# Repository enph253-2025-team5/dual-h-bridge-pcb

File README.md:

# Dual H-Bridge PCB

Dual h-bridge design with a PWM signal and direction bit for controlling two motors.

Similar to Greg Reid's 2025 h-bridge design, without relying on tripping the overcurrent protection. Instead, this design duplicates the incoming PWM signal, sends one to each of the low side h-bridge MOSFETs, then pulls the gate with the enhanced high side MOSFET low (avoiding shoot-through). 

Based on many factors (motor inertia, gate driver response, optocoupler distortion) the PWM frequency should be limited on the order of 100 Hz.
Intended motor battery configuration of 4S.

**BOM, Schematic, and PCB drawings in the latest release.**

## Images

Designed by George Sleen.

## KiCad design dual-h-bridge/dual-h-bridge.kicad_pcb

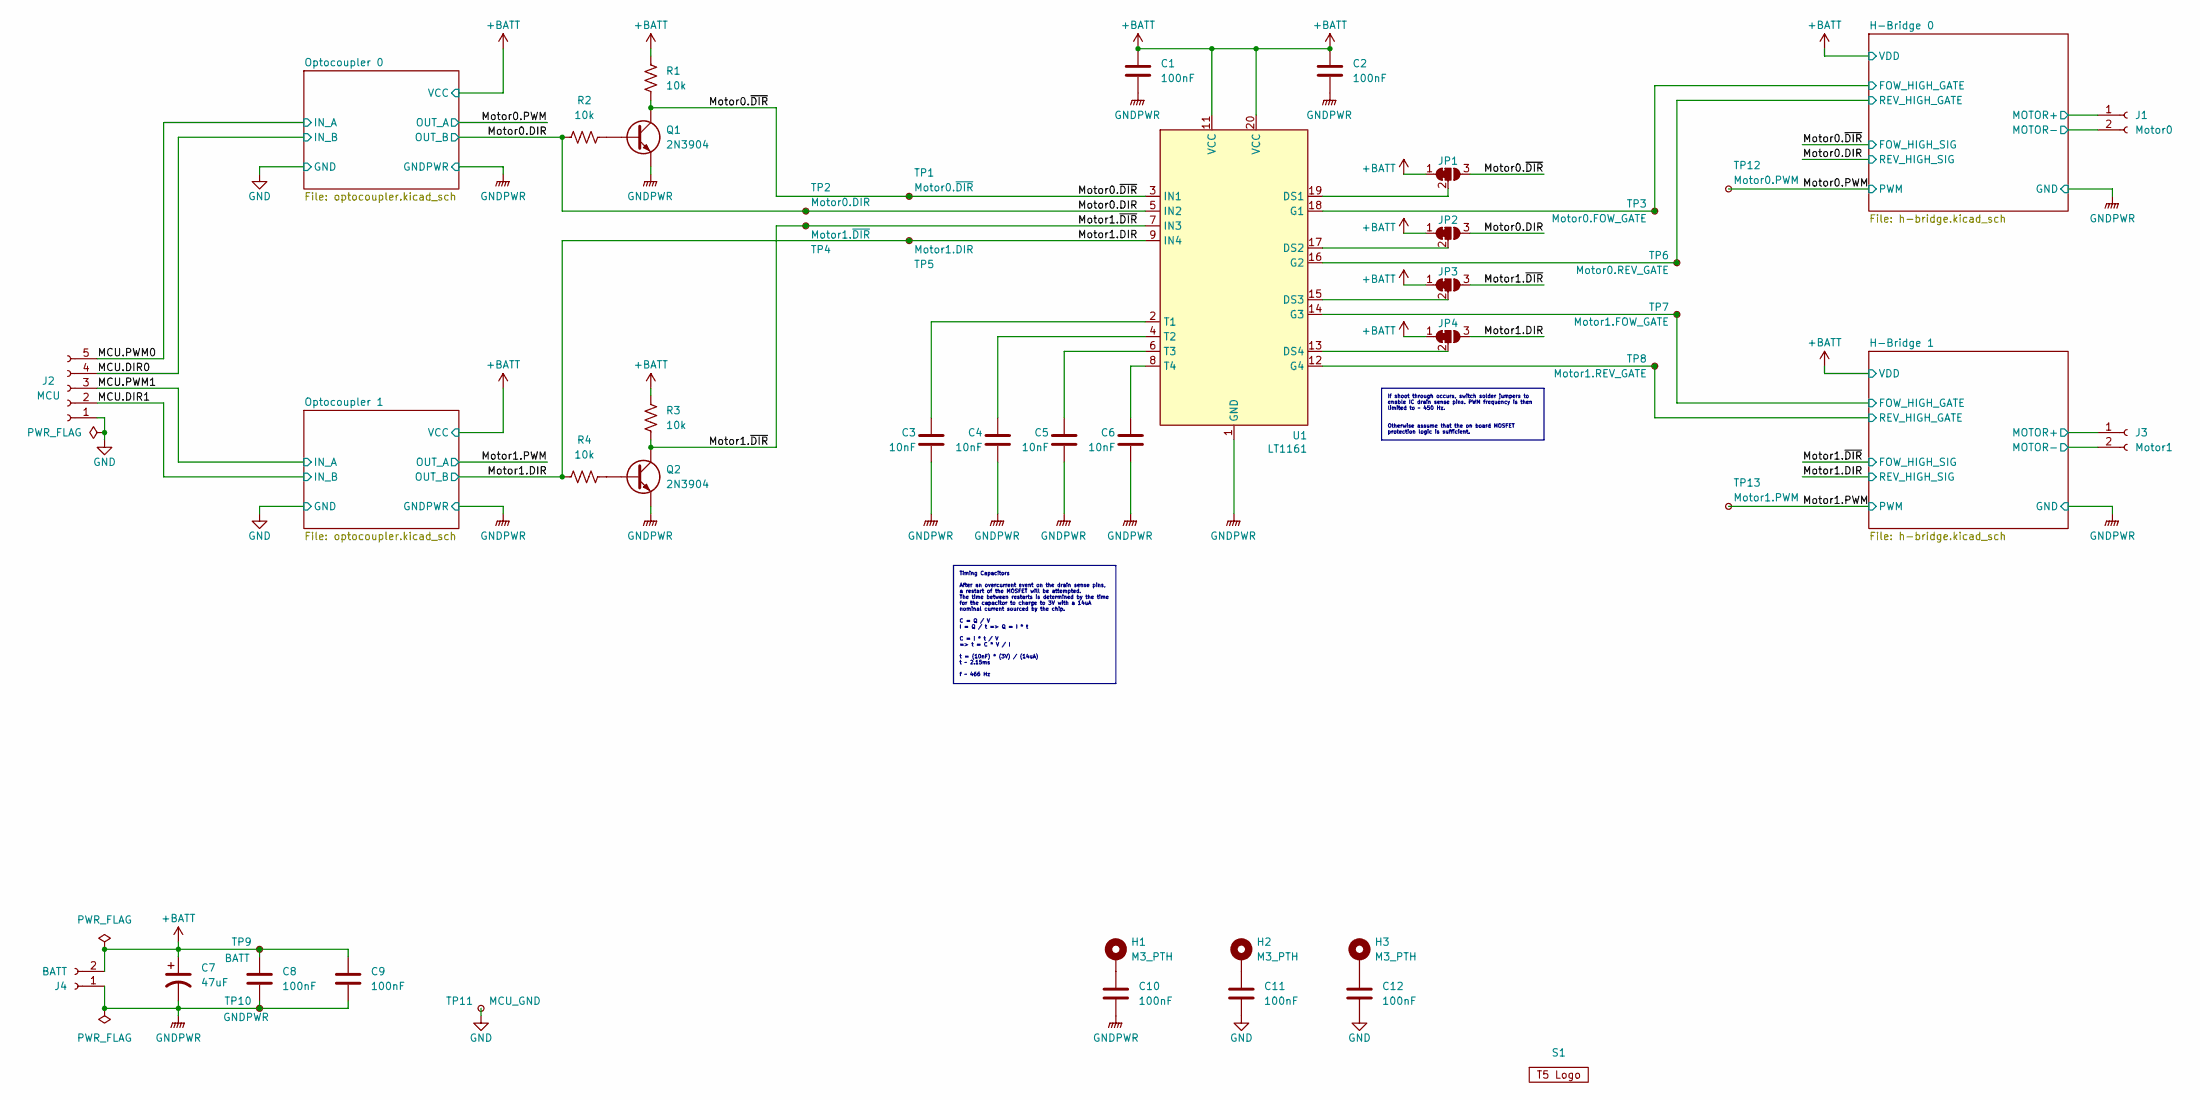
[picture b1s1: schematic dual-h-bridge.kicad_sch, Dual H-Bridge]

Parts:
C1, C2, C8, C9, C10, C11, C12: 100nF; C_Disc_D3.0mm_W2.0mm_P2.50mm
C3, C4, C5, C6: 10nF; C_Disc_D3.0mm_W2.0mm_P2.50mm
C7: 47uF; CP_Radial_D5.0mm_P2.00mm
H1, H2, H3: M3_PTH; MountingHole_3.2mm_M3_Pad
J1: Motor0; JST_XH_S2B-XH-A-1_1x02_P2.50mm_Horizontal
J2: MCU; JST_XH_B5B-XH-A_1x05_P2.50mm_Vertical
J3: Motor1; JST_XH_S2B-XH-A-1_1x02_P2.50mm_Horizontal
J4: BATT; JST_XH_B2B-XH-A_1x02_P2.50mm_Vertical
JP1: Motor0_FOW; SolderJumper-3_P1.3mm_Bridged12_RoundedPad1.0x1.5mm
JP2: MOTOR0_REV; SolderJumper-3_P1.3mm_Bridged12_RoundedPad1.0x1.5mm
JP3: MOTOR1_FOW; SolderJumper-3_P1.3mm_Bridged12_RoundedPad1.0x1.5mm
JP4: MOTOR1_REV; SolderJumper-3_P1.3mm_Bridged12_RoundedPad1.0x1.5mm
Q1, Q2: 2N3904; TO-92_Inline
R1, R2, R3, R4: 10k; R_Axial_DIN0309_L9.0mm_D3.2mm_P12.70mm_Horizontal
S1: Logo; ENPH253_Logo_Small
TP1: Motor0.~{DIR}; TestPoint_Pad_1.5x1.5mm
TP2: Motor0.DIR; TestPoint_Pad_1.5x1.5mm
TP3: Motor0.FOW_GATE; TestPoint_Pad_1.5x1.5mm
TP4: Motor1.~{DIR}; TestPoint_Pad_1.5x1.5mm
TP5: Motor1.DIR; TestPoint_Pad_1.5x1.5mm
TP6: Motor0.REV_GATE; TestPoint_Pad_1.5x1.5mm
TP7: Motor1.FOW_GATE; TestPoint_Pad_1.5x1.5mm
TP8: Motor1.REV_GATE; TestPoint_Pad_1.5x1.5mm
TP9: BATT; TestPoint_Pad_1.5x1.5mm
TP10: GNDPWR; TestPoint_Pad_1.5x1.5mm
TP11: MCU_GND; TestPoint_Pad_1.5x1.5mm
TP12: Motor0.PWM; TestPoint_Pad_1.5x1.5mm
TP13: Motor1.PWM; TestPoint_Pad_1.5x1.5mm
U1: LT1161; DIP-20_W7.62mm_LongPads

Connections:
+BATT: C1.1, C2.1, C7.1, C8.1, C9.1, J4.2, JP1.1 (A), JP2.1 (A), JP3.1 (A), JP4.1 (A), R1.1, R3.1, TP9.1, U1.11 (VCC), U1.20 (VCC); also elsewhere on the board
/H-Bridge 0/FOW_HIGH_GATE: TP3.1, U1.18 (G1); also elsewhere on the board
/H-Bridge 0/MOTOR+: J1.1; also elsewhere on the board
/H-Bridge 0/MOTOR-: J1.2; also elsewhere on the board
/H-Bridge 0/REV_HIGH_GATE: TP6.1, U1.16 (G2); also elsewhere on the board
/H-Bridge 1/FOW_HIGH_GATE: TP7.1, U1.14 (G3); also elsewhere on the board
/H-Bridge 1/MOTOR+: J3.1; also elsewhere on the board
/H-Bridge 1/MOTOR-: J3.2; also elsewhere on the board
/H-Bridge 1/REV_HIGH_GATE: TP8.1, U1.12 (G4); also elsewhere on the board
/MCU.DIR0: J2.4; also elsewhere on the board
/MCU.DIR1: J2.2; also elsewhere on the board
/MCU.PWM0: J2.5; also elsewhere on the board
/MCU.PWM1: J2.3; also elsewhere on the board
/Motor0.DIR: JP2.3 (B), R2.1, TP2.1, U1.5 (IN2); also elsewhere on the board
/Motor0.PWM: TP12.1; also elsewhere on the board
/Motor0.~DIR: JP1.3 (B), Q1.3 (C), R1.2, TP1.1, U1.3 (IN1); also elsewhere on the board
/Motor1.DIR: JP4.3 (B), R4.1, TP5.1, U1.9 (IN4); also elsewhere on the board
/Motor1.PWM: TP13.1; also elsewhere on the board
/Motor1.~DIR: JP3.3 (B), Q2.3 (C), R3.2, TP4.1, U1.7 (IN3); also elsewhere on the board
GND: C11.2, C12.2, J2.1, TP11.1; also elsewhere on the board
GNDPWR: C1.2, C2.2, C3.2, C4.2, C5.2, C6.2, C7.2, C8.2, C9.2, C10.2, J4.1, Q1.1 (E), Q2.1 (E), TP10.1, U1.1 (GND), U1.10 (GND); also elsewhere on the board
unnamed: C10.1, H1.1
unnamed: C11.1, H2.1
unnamed: C12.1, H3.1
unnamed: JP1.2 (C), U1.19 (DS1)
unnamed: JP2.2 (C), U1.17 (DS2)
unnamed: JP3.2 (C), U1.15 (DS3)
unnamed: JP4.2 (C), U1.13 (DS4)
unnamed: Q1.2 (B), R2.2
unnamed: Q2.2 (B), R4.2
unnamed: C3.1, U1.2 (T1)
unnamed: C4.1, U1.4 (T2)
unnamed: C5.1, U1.6 (T3)
unnamed: C6.1, U1.8 (T4)

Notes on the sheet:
If shoot through occurs, switch solder jumpers to enable IC drain sense pins. PWM frequency is then limited to ~ 450 Hz. Otherwise assume that the on board MOSFET protection logic is sufficient.
Timing Capacitors After an overcurrent event on the drain sense pins, a restart of the MOSFET will be attempted. The time between restarts is determined by the time for the capacitor to charge to 3V with a 14uA nominal current sourced by the chip. C = Q / V I = Q / t => Q = I * t C = I * t / V => t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

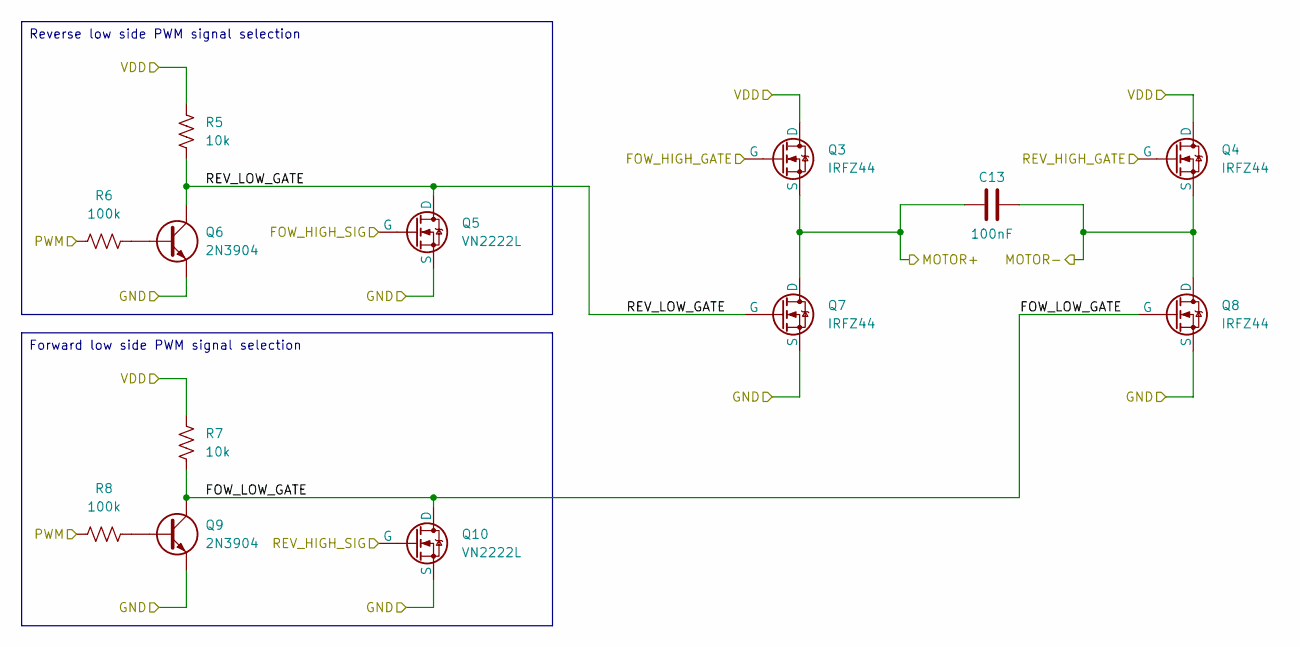
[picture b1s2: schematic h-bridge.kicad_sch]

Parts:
C13: 100nF; C_Disc_D3.0mm_W2.0mm_P2.50mm
Q3, Q4, Q7, Q8: IRFZ44; TO-220-3_Vertical
Q5, Q10: VN2222L; TO-92_Inline
Q6, Q9: 2N3904; TO-92_Inline
R5, R7: 10k; R_Axial_DIN0309_L9.0mm_D3.2mm_P12.70mm_Horizontal
R6, R8: 100k; R_Axial_DIN0309_L9.0mm_D3.2mm_P12.70mm_Horizontal

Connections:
+BATT: Q3.2 (D), Q4.2 (D), R5.1, R7.1; also elsewhere on the board
/H-Bridge 0/FOW_HIGH_GATE: Q3.1 (G); also elsewhere on the board
/H-Bridge 0/FOW_LOW_GATE: Q8.1 (G), Q9.3 (C), Q10.3 (D), R7.2
/H-Bridge 0/MOTOR+: C13.1, Q3.3 (S), Q7.2 (D); also elsewhere on the board
/H-Bridge 0/MOTOR-: C13.2, Q4.3 (S), Q8.2 (D); also elsewhere on the board
/H-Bridge 0/REV_HIGH_GATE: Q4.1 (G); also elsewhere on the board
/H-Bridge 0/REV_LOW_GATE: Q5.3 (D), Q6.3 (C), Q7.1 (G), R5.2
/Motor0.DIR: Q10.2 (G); also elsewhere on the board
/Motor0.PWM: R6.1, R8.1; also elsewhere on the board
/Motor0.~DIR: Q5.2 (G); also elsewhere on the board
GNDPWR: Q5.1 (S), Q6.1 (E), Q7.3 (S), Q8.3 (S), Q9.1 (E), Q10.1 (S); also elsewhere on the board
unnamed: Q6.2 (B), R6.2
unnamed: Q9.2 (B), R8.2

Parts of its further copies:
C14: 100nF; C_Disc_D3.0mm_W2.0mm_P2.50mm
Q11, Q12, Q15, Q16: IRFZ44; TO-220-3_Vertical
Q13, Q18: VN2222L; TO-92_Inline
Q14, Q17: 2N3904; TO-92_Inline
R9, R11: 10k; R_Axial_DIN0309_L9.0mm_D3.2mm_P12.70mm_Horizontal
R10, R12: 100k; R_Axial_DIN0309_L9.0mm_D3.2mm_P12.70mm_Horizontal

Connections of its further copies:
+BATT: Q11.2 (D), Q12.2 (D), R9.1, R11.1; also elsewhere on the board
/H-Bridge 1/FOW_HIGH_GATE: Q11.1 (G); also elsewhere on the board
/H-Bridge 1/FOW_LOW_GATE: Q16.1 (G), Q17.3 (C), Q18.3 (D), R11.2
/H-Bridge 1/MOTOR+: C14.1, Q11.3 (S), Q15.2 (D); also elsewhere on the board
/H-Bridge 1/MOTOR-: C14.2, Q12.3 (S), Q16.2 (D); also elsewhere on the board
/H-Bridge 1/REV_HIGH_GATE: Q12.1 (G); also elsewhere on the board
/H-Bridge 1/REV_LOW_GATE: Q13.3 (D), Q14.3 (C), Q15.1 (G), R9.2
/Motor1.DIR: Q18.2 (G); also elsewhere on the board
/Motor1.PWM: R10.1, R12.1; also elsewhere on the board
/Motor1.~DIR: Q13.2 (G); also elsewhere on the board
GNDPWR: Q13.1 (S), Q14.1 (E), Q15.3 (S), Q16.3 (S), Q17.1 (E), Q18.1 (S); also elsewhere on the board
unnamed: Q14.2 (B), R10.2
unnamed: Q17.2 (B), R12.2

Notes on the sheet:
Reverse low side PWM signal selection
Forward low side PWM signal selection

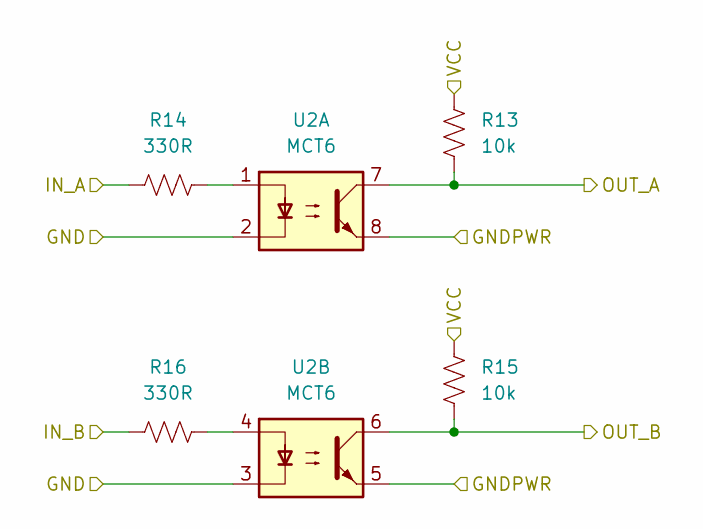
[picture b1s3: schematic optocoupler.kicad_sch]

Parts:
R13, R15: 10k; R_Axial_DIN0309_L9.0mm_D3.2mm_P12.70mm_Horizontal
R14, R16: 330R; R_Axial_DIN0309_L9.0mm_D3.2mm_P12.70mm_Horizontal
U2: MCT6; DIP-8_W7.62mm_LongPads

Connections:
+BATT: R13.2, R15.2; also elsewhere on the board
/MCU.DIR0: R16.1; also elsewhere on the board
/MCU.PWM0: R14.1; also elsewhere on the board
/Motor0.DIR: R15.1, U2.6; also elsewhere on the board
/Motor0.PWM: R13.1, U2.7; also elsewhere on the board
GND: U2.2, U2.3; also elsewhere on the board
GNDPWR: U2.5, U2.8; also elsewhere on the board
unnamed: R14.2, U2.1
unnamed: R16.2, U2.4

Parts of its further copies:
R17, R19: 10k; R_Axial_DIN0309_L9.0mm_D3.2mm_P12.70mm_Horizontal
R18, R20: 330R; R_Axial_DIN0309_L9.0mm_D3.2mm_P12.70mm_Horizontal
U3: MCT6; DIP-8_W7.62mm_LongPads

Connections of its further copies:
+BATT: R17.2, R19.2; also elsewhere on the board
/MCU.DIR1: R20.1; also elsewhere on the board
/MCU.PWM1: R18.1; also elsewhere on the board
/Motor1.DIR: R19.1, U3.6; also elsewhere on the board
/Motor1.PWM: R17.1, U3.7; also elsewhere on the board
GND: U3.2, U3.3; also elsewhere on the board
GNDPWR: U3.5, U3.8; also elsewhere on the board
unnamed: R18.2, U3.1
unnamed: R20.2, U3.4

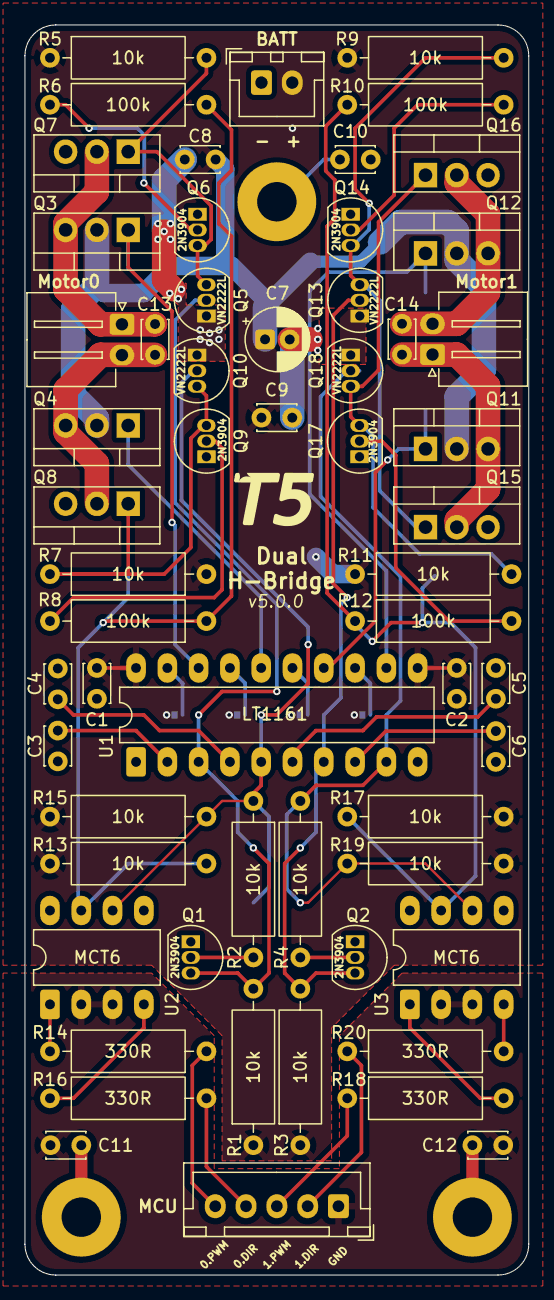
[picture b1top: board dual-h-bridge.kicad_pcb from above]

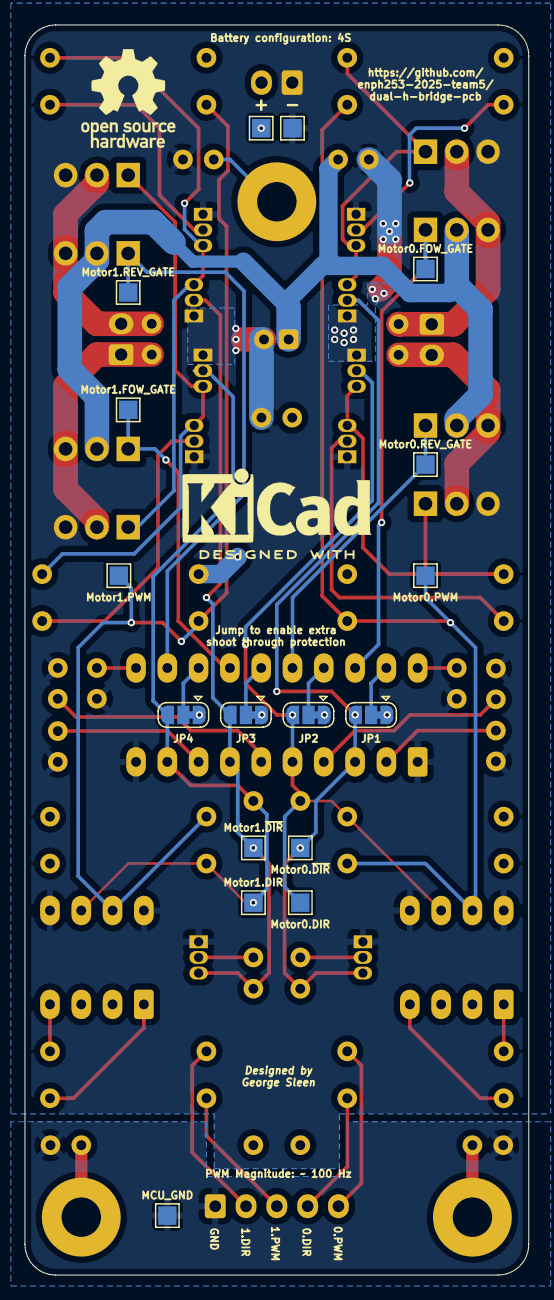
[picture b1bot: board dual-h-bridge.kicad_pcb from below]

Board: 2 copper layers, 40.9 x 101.5 mm, 80 parts (17 on the bottom side), 46 nets.

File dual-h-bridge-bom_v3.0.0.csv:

"Value","Qty","Reference","Footprint"
"100nF","9","C1,C2,C8,C9,C10,C11,C12,C13,C14","Capacitor_THT:C_Disc_D3.0mm_W2.0mm_P2.50mm"
"10nF","4","C3,C4,C5,C6","Capacitor_THT:C_Disc_D3.0mm_W2.0mm_P2.50mm"
"LT1161","1","U1","Package_DIP:DIP-20_W7.62mm_LongPads"
"MCT6","2","U2,U3","Package_DIP:DIP-8_W7.62mm_LongPads"
"Motor0","1","J1","GS_Connectors:JST_XH_S2B-XH-A-1_1x02_P2.50mm_Horizontal"
"Motor1","1","J2","GS_Connectors:JST_XH_S2B-XH-A-1_1x02_P2.50mm_Horizontal"
"BATT","1","J3","Connector_JST:JST_XH_B2B-XH-A_1x02_P2.50mm_Vertical"
"MCU","1","J4","Connector_JST:JST_XH_B5B-XH-A_1x05_P2.50mm_Vertical"
"VN2222L","4","Q6,Q10,Q14,Q18","Package_TO_SOT_THT:TO-92_Inline"
"IRFZ44","8","Q3,Q4,Q7,Q8,Q11,Q12,Q15,Q16","Package_TO_SOT_THT:TO-220-3_Vertical"
"2N3904","6","Q1,Q2,Q5,Q9,Q13,Q17","Package_TO_SOT_THT:TO-92_Inline"
"47uF","1","C7","Capacitor_THT:CP_Radial_D5.0mm_P2.00mm"
"10k","10","R1,R3,R5,R7,R9,R11,R14,R16,R18,R20","Resistor_THT:R_Axial_DIN0309_L9.0mm_D3.2mm_P12.70mm_Horizontal"
"100k","6","R2,R4,R6,R10,R21,R22","Resistor_THT:R_Axial_DIN0309_L9.0mm_D3.2mm_P12.70mm_Horizontal"
"330R","4","R13,R15,R17,R19","Resistor_THT:R_Axial_DIN0309_L9.0mm_D3.2mm_P12.70mm_Horizontal"

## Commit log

2025-05-16 update git ignore to NOT ignore production outputs
2025-05-16 Create project structure
2025-06-06 Change project name
2025-06-06 Create H-Bridge schematic
2025-06-06 Finish optocoupler and gate-driver
2025-06-06 Finish H-Bridge schematic
2025-06-15 Change h-bridge design to newer version
2025-06-15 Fix some ERC issues
2025-06-19 Update PWM signal selection to avoid an accidental resistor divider
2025-06-19 Finish layout
2025-06-20 Generate schematic pdf
2025-06-20 Add engineering drawings for the PCB
2025-06-20 Change name and produce production outputs
2025-06-20 Fix some production outputs
2025-06-22 minor changes to back silkscreen
2025-06-22 Update clarity of README
2025-06-22 Update README.md to reflect most current release
2025-07-02 Update to right angle motor connectors
2025-07-02 Change to new connector standard
2025-07-03 Change README.md
2025-07-05 Fix potentially inverted H-Bridge direction bit
2025-07-06 Update silkscreen
2025-07-09 Fix optocoupler hardware issue
2025-07-09 Generate production outputs
2025-07-10 Some small updates
2025-07-10 More changes
2025-07-11 Fix all hardware issues and generate final release source files
2025-07-11 Generate release package with all hardware issues fixed
2025-07-17 Fix source and drain being swapped on small signal mosfet
2025-07-17 Generate v5.0.0 production files
